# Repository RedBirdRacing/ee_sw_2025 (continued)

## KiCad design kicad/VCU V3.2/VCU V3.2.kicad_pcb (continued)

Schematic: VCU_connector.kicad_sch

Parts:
J1, J2: HD241_24pin

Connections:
+5V: J1.19, J2.3, J2.4; also elsewhere on the board
+12V: J1.1, J1.2, J1.9, J1.10, J1.17, J1.18; also elsewhere on the board
APPS_3VGND: J2.18; also elsewhere on the board
APPS_3VIN: J2.2; also elsewhere on the board
APPS_3VOUT: J2.10; also elsewhere on the board
APPS_5VGND: J2.17; also elsewhere on the board
APPS_5VIN: J2.1; also elsewhere on the board
APPS_5VOUT: J2.9; also elsewhere on the board
BRAKE_AIN: J2.11; also elsewhere on the board
CAN1+: J2.6; also elsewhere on the board
CAN1-: J2.5; also elsewhere on the board
CAN2+: J2.8, J2.16; also elsewhere on the board
CAN2-: J2.7, J2.15; also elsewhere on the board
CAN3+: J2.14; also elsewhere on the board
CAN3-: J2.13; also elsewhere on the board
CURRENT_AIN: J2.12; also elsewhere on the board
DIN_1: J2.21; also elsewhere on the board
DIN_2: J2.22; also elsewhere on the board
DIN_3: J2.23; also elsewhere on the board
GND: J1.7, J1.8, J1.15, J1.16, J1.23, J1.24, J2.19, J2.20; also elsewhere on the board
IGN_12V: J2.24; also elsewhere on the board
PDU_1: J1.3, J1.11; also elsewhere on the board
PDU_2: J1.4, J1.12; also elsewhere on the board
PDU_3: J1.5, J1.13; also elsewhere on the board
PDU_4: J1.6, J1.14; also elsewhere on the board
PDU_5: J1.20; also elsewhere on the board
PDU_6: J1.21; also elsewhere on the board
PDU_7: J1.22; also elsewhere on the board

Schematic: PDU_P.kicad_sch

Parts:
D2: LED; LED_0805_2012Metric_Pad1.45x1.40mm_HandSolder
Q1: MMBT3904; SOT-23
Q2: BSC030P03NS3; Infineon_PG-TDSON-8_6.15x5.15mm
R5, R6, R7: 1k; R_0805_2012Metric_Pad1.20x1.40mm_HandSolder_L
R8: 100k; R_0805_2012Metric_Pad1.20x1.40mm_HandSolder_L

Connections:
+12V: D2.2 (A), Q2.1 (S), Q2.2 (S), Q2.3 (S), R7.1; also elsewhere on the board
/PDU_P4_1/PDU_1/MOS_GATE: Q1.3 (C), Q2.4 (G), R6.2, R7.2, R8.1
/PDU_P4_1/PDU_1/SIGNAL: R5.1; also elsewhere on the board
GND: Q1.2 (E), R8.2; also elsewhere on the board
unnamed: D2.1 (K), R6.1
unnamed: Q1.1 (B), R5.2
PDU_1: Q2.5 (D), Q2.6 (D), Q2.7 (D), Q2.8 (D); also elsewhere on the board

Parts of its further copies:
D3, D4, D5: LED; LED_0805_2012Metric_Pad1.45x1.40mm_HandSolder
Q3, Q5, Q7: MMBT3904; SOT-23
Q4, Q6, Q8: BSC030P03NS3; Infineon_PG-TDSON-8_6.15x5.15mm
R9, R10, R11, R13, R14, R15, R17, R18, R19: 1k; R_0805_2012Metric_Pad1.20x1.40mm_HandSolder_L
R12, R16, R20: 100k; R_0805_2012Metric_Pad1.20x1.40mm_HandSolder_L

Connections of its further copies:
+12V: D3.2 (A), D4.2 (A), D5.2 (A), Q4.1 (S), Q4.2 (S), Q4.3 (S), Q6.1 (S), Q6.2 (S), Q6.3 (S), Q8.1 (S), Q8.2 (S), Q8.3 (S), R11.1, R15.1, R19.1; also elsewhere on the board
/PDU_P4_1/PDU_2/MOS_GATE: Q3.3 (C), Q4.4 (G), R10.2, R11.2, R12.1
/PDU_P4_1/PDU_2/SIGNAL: R9.1; also elsewhere on the board
/PDU_P4_1/PDU_3/MOS_GATE: Q5.3 (C), Q6.4 (G), R14.2, R15.2, R16.1
/PDU_P4_1/PDU_3/SIGNAL: R13.1; also elsewhere on the board
/PDU_P4_1/PDU_4/MOS_GATE: Q7.3 (C), Q8.4 (G), R18.2, R19.2, R20.1
/PDU_P4_1/PDU_4/SIGNAL: R17.1; also elsewhere on the board
GND: Q3.2 (E), Q5.2 (E), Q7.2 (E), R12.2, R16.2, R20.2; also elsewhere on the board
unnamed: D3.1 (K), R10.1
unnamed: D4.1 (K), R14.1
unnamed: D5.1 (K), R18.1
unnamed: Q3.1 (B), R9.2
unnamed: Q5.1 (B), R13.2
unnamed: Q7.1 (B), R17.2
PDU_2: Q4.5 (D); also elsewhere on the board
PDU_3: Q6.5 (D); also elsewhere on the board
PDU_4: Q8.5 (D); also elsewhere on the board

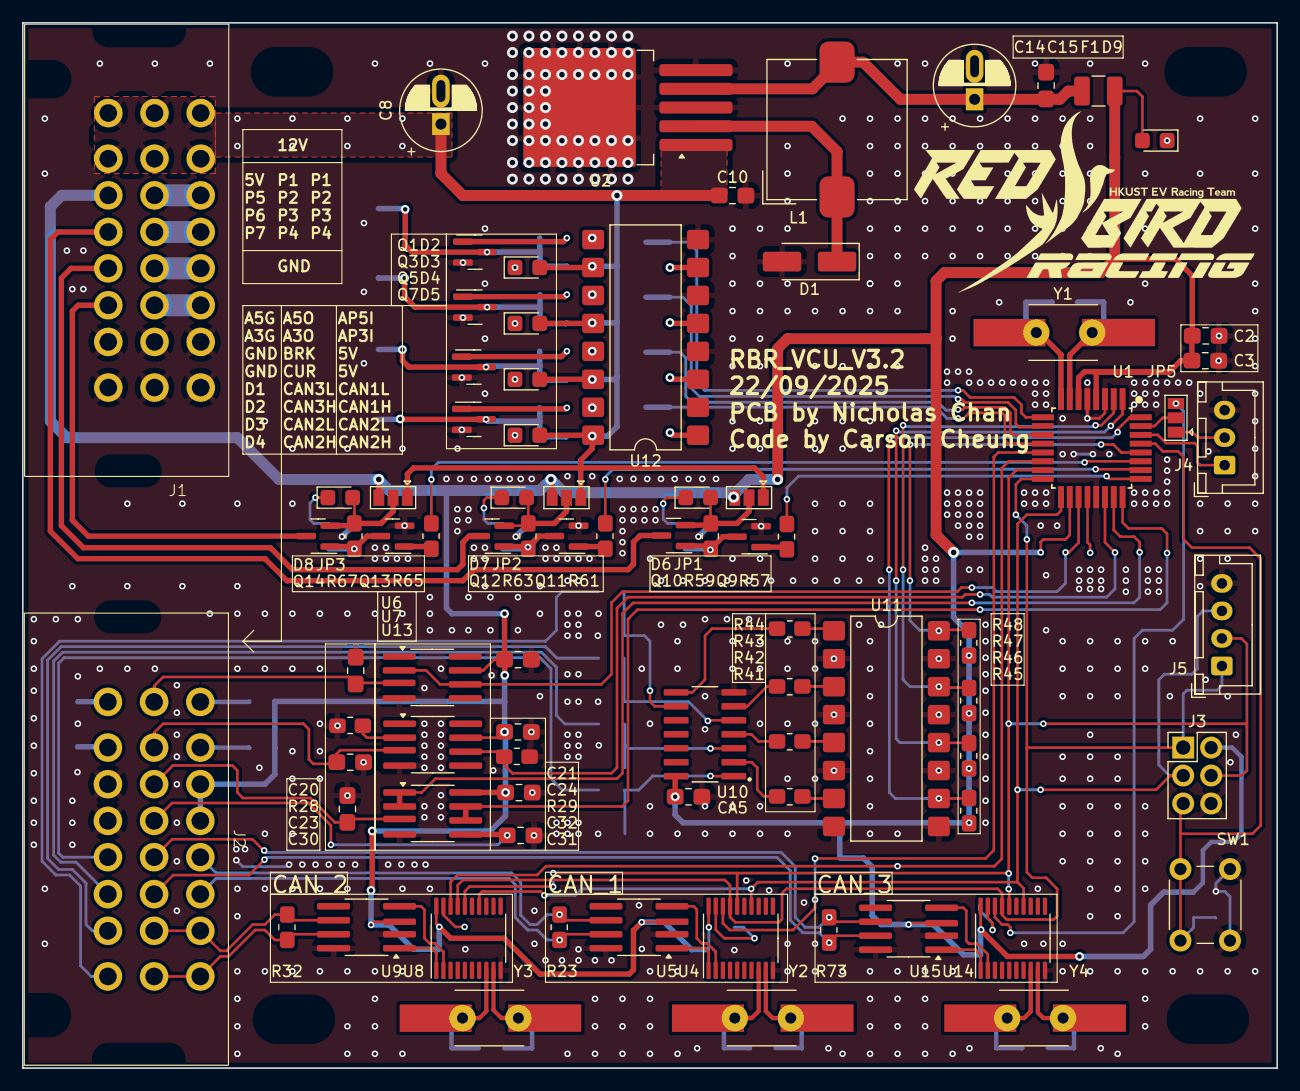
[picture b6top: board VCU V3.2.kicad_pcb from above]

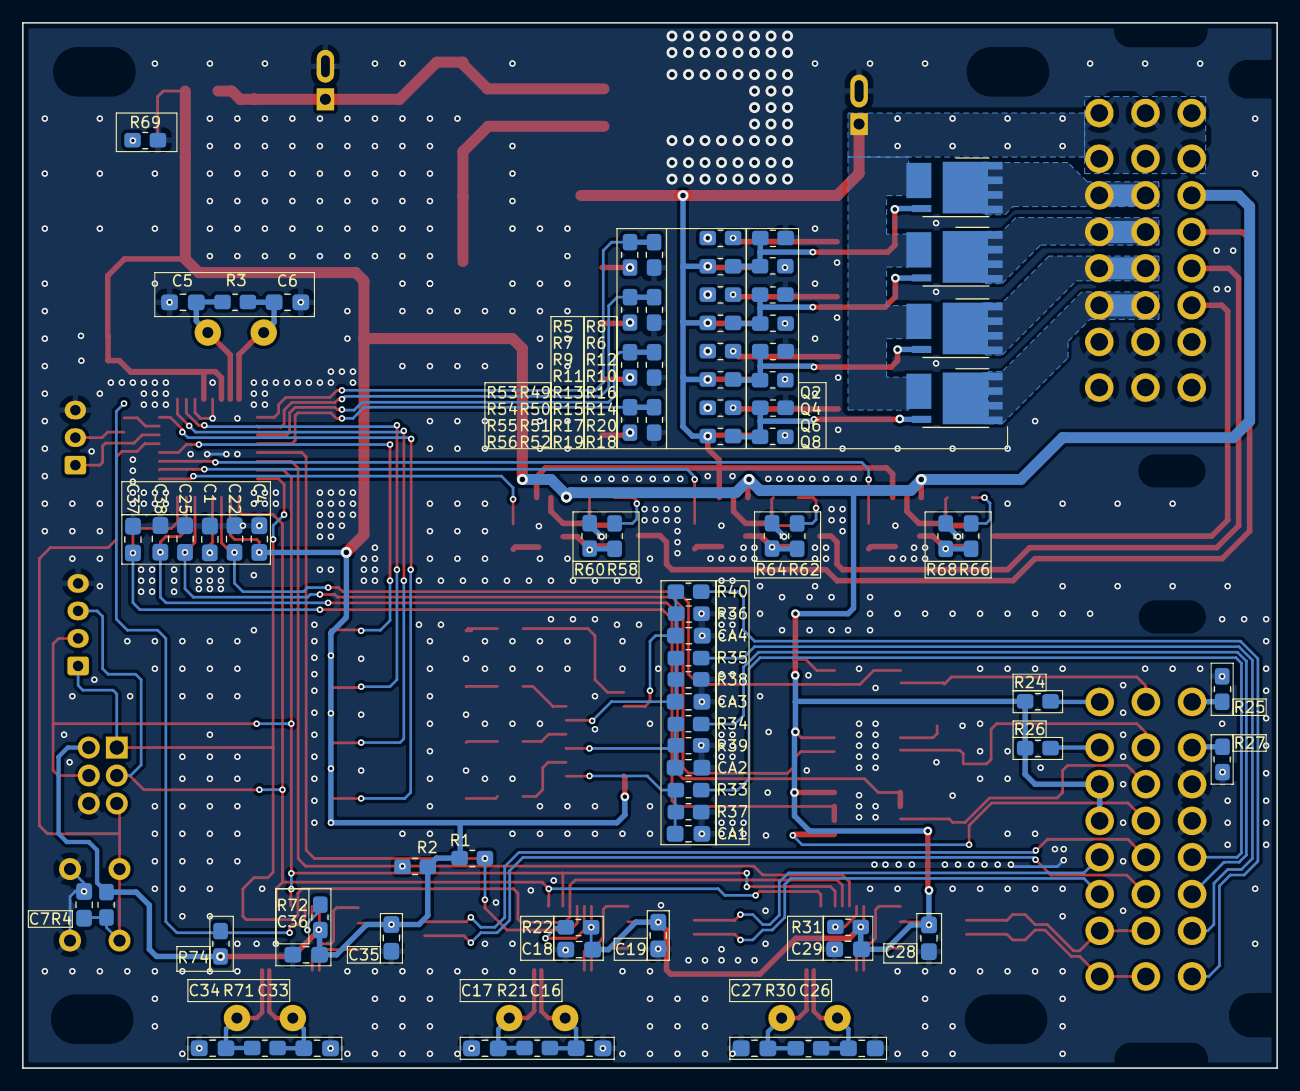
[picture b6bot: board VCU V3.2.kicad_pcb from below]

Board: 2 copper layers, 114.0 x 95.0 mm, 169 parts (83 on the bottom side), 119 nets.

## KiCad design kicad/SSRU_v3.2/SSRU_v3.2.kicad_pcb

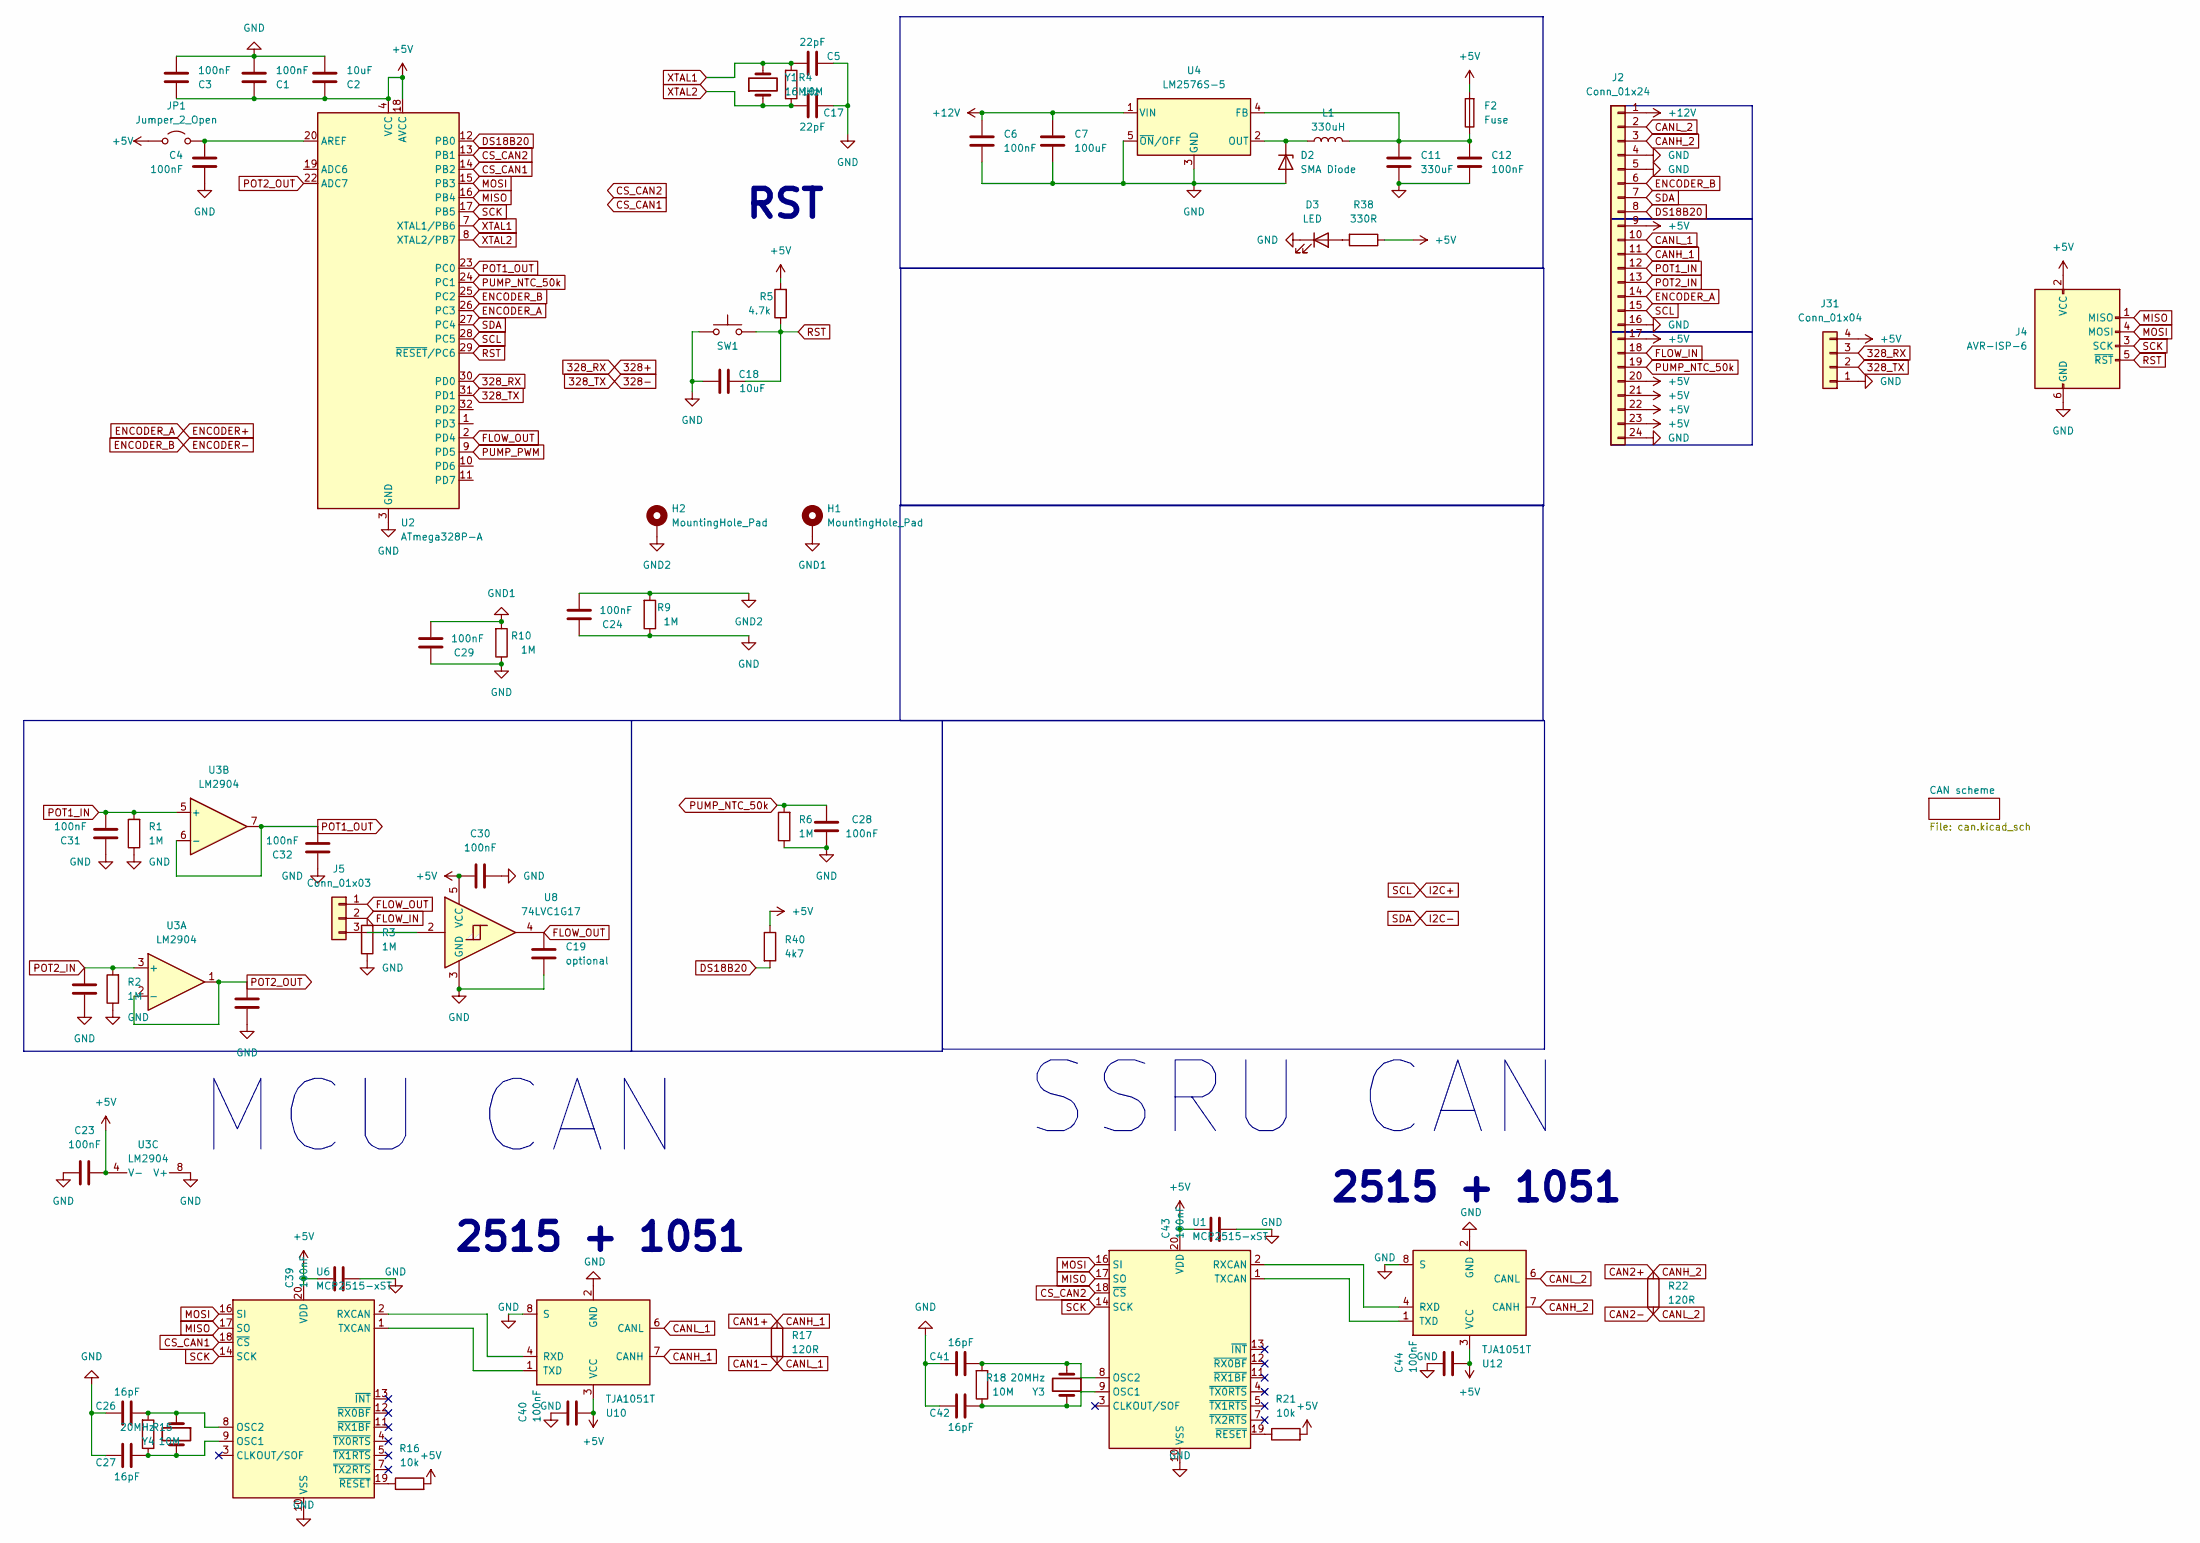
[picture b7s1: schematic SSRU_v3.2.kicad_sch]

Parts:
C1, C3, C4, C6, C12, C23, C24, C28, C29, C30, C31, C32, C36, C37, C39, C40, C43, C44: 100nF; C_0805_2012Metric_Pad1.18x1.45mm_HandSolder_L
C2, C18: 10uF; C_0805_2012Metric_Pad1.18x1.45mm_HandSolder_L
C5, C17: 22pF; C_0805_2012Metric_Pad1.18x1.45mm_HandSolder_L
C7: 100uF; CP_Radial_D6.3mm_P2.50mm_handsolder
C11: 330uF; CP_Radial_D6.3mm_P2.50mm_handsolder
C19: optional; C_0805_2012Metric_Pad1.18x1.45mm_HandSolder_L
C26, C27, C41, C42: 16pF; C_0805_2012Metric_Pad1.18x1.45mm_HandSolder_L
D2: SMA Diode; D_SMA_Handsoldering
D3: LED; LED_0805_2012Metric_Pad1.45x1.40mm_HandSolder
F2: Fuse; Fuse_1210_3225Metric_Pad1.42x2.65mm_HandSolder
H1, H2: MountingHole_Pad; MountingHole_3.2mm_M3_ISO14580_Pad
J2: Conn_01x24; HD241_24pin
J4: AVR-ISP-6; PinHeader_2x03_P2.54mm_Vertical
J5: Conn_01x03; SolderJumper-3_P1.3mm_Open_Pad1.0x1.5mm
J31: Conn_01x04; JST_XH_B4B-XH-A_1x04_P2.50mm_Vertical
JP1: Jumper_2_Open; SolderJumper-2_P1.3mm_Open_Pad1.0x1.5mm
L1: 330uH; L_10.4x10.4_H4.8
R1, R2, R3, R6, R9, R10: 1M; R_0805_2012Metric_Pad1.20x1.40mm_HandSolder_L
R4, R15, R18: 10M; R_0805_2012Metric_Pad1.20x1.40mm_HandSolder_L
R5: 4.7k; R_0805_2012Metric_Pad1.20x1.40mm_HandSolder_L
R16, R21: 10k; R_0805_2012Metric_Pad1.20x1.40mm_HandSolder_L
R17, R22: 120R; R_0805_2012Metric_Pad1.20x1.40mm_HandSolder_L
R38: 330R; R_0805_2012Metric_Pad1.20x1.40mm_HandSolder_L
R40: 4k7; R_0805_2012Metric_Pad1.20x1.40mm_HandSolder_L
SW1: SW_Push; SW_PUSH_6mm_H5mm
U1, U6: MCP2515-xST; TSSOP-20_4.4x6.5mm_P0.65mm
U2: ATmega328P-A; TQFP-32_7x7mm_P0.8mm_L
U3: LM2904; SOIC-8_3.9x4.9mm_P1.27mm_RMC_Handsolder
U4: LM2576S-5; TO-263-5_TabPin3_Handsolder
U8: 74LVC1G17; SOT-23-5_HandSoldering_Extended_RMC
U10, U12: TJA1051T; SOIC-8_3.9x4.9mm_P1.27mm_RMC_Handsolder
Y1: 16MHz; Crystal_HC49-U_Vertical_W_SMD
Y3, Y4: 20MHz; Crystal_HC49-U_Vertical_W_SMD

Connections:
328+: J31.3, U2.30 (PD0)
328-: J31.2, U2.31 (PD1)
+5V: C1.2, C2.2, C3.2, C23.2, C30.2, C39.2, C40.1, C43.2, C44.1, F2.2, J2.9, J2.17, J2.20, J2.21, J2.22, J2.23, J4.2 (VCC), J31.4, JP1.1 (A), R5.2, R16.2, R21.2, R38.1, R40.1, U1.20 (VDD), U2.4 (VCC), U2.6 (VCC), U2.18 (AVCC), U3.4 (V-), U6.20 (VDD), U8.5 (VCC), U10.3 (VCC), U12.3 (VCC)
+12V: C6.2, C7.1, J2.1, U4.1 (VIN)
CAN1+: J2.11, R17.2, U10.7 (CANH)
CAN1-: J2.10, R17.1, U10.6 (CANL)
CAN2+: J2.3, R22.2, U12.7 (CANH)
CAN2-: J2.2, R22.1, U12.6 (CANL)
CS_CAN1: U2.14 (PB2), U6.18 (~CS)
CS_CAN2: U1.18 (~CS), U2.13 (PB1)
DS18B20: J2.8, R40.2, U2.12 (PB0)
ENCODER+: J2.14, U2.26 (PC3)
ENCODER-: J2.6, U2.25 (PC2)
FLOW_IN: J2.18, J5.2, R3.2
FLOW_OUT: C19.2, J5.1, U2.2 (PD4), U8.4
GND: C1.1, C2.1, C3.1, C4.1, C5.1, C6.1, C7.2, C11.2, C12.1, C17.1, C18.1, C19.1, C23.1, C24.1, C26.1, C27.1, C28.2, C29.1, C30.1, C31.1, C32.1, C36.1, C37.1, C39.1, C40.2, C41.1, C42.1, C43.1, C44.2, D2.2 (A), D3.1 (K), J2.4, J2.5, J2.16, J2.24, J4.6 (GND), J31.1, R1.1, R2.1, R3.1, R6.1, R9.1, R10.1, SW1.1, U1.10 (VSS), U2.3 (GND), U2.5 (GND), U2.21 (GND), U3.8 (V+), U4.3 (GND), U4.5 (~ON/OFF), U6.10 (VSS), U8.3 (GND), U10.2 (GND), U10.8 (S), U12.2 (GND), U12.8 (S)
GND1: C29.2, H1.1, R10.2
GND2: C24.2, H2.1, R9.2
I2C+: J2.15, U2.28 (PC5)
I2C-: J2.7, U2.27 (PC4)
MISO: J4.1 (MISO), U1.17 (SO), U2.16 (PB4), U6.17 (SO)
MOSI: J4.4 (MOSI), U1.16 (SI), U2.15 (PB3), U6.16 (SI)
unnamed: D2.1 (K), L1.1, U4.2 (OUT)
unnamed: D3.2 (A), R38.2
unnamed: J5.3, U8.2
unnamed: C4.2, JP1.2 (B), U2.20 (AREF)
unnamed: C42.2, R18.1, U1.9 (OSC1), Y3.2
unnamed: C41.2, R18.2, U1.8 (OSC2), Y3.1
unnamed: U1.2 (RXCAN), U12.4 (RXD)
unnamed: U1.1 (TXCAN), U12.1 (TXD)
unnamed: R21.1, U1.19 (~RESET)
unnamed: C11.1, C12.2, F2.1, L1.2, U4.4 (FB)
unnamed: C27.2, R15.1, U6.9 (OSC1), Y4.2
unnamed: C26.2, R15.2, U6.8 (OSC2), Y4.1
unnamed: R16.1, U6.19 (~RESET)
unnamed: U6.2 (RXCAN), U10.4 (RXD)
unnamed: U6.1 (TXCAN), U10.1 (TXD)
POT1_IN: C31.2, J2.12, R1.2, U3.5 (+)
POT1_OUT: C32.2, U2.23 (PC0), U3.6 (-), U3.7
POT2_IN: C36.2, J2.13, R2.2, U3.3 (+)
POT2_OUT: C37.2, U2.22 (ADC7), U3.1, U3.2 (-)
PUMP_NTC_50k: C28.1, J2.19, R6.2, U2.24 (PC1)
PUMP_PWM: U2.9 (PD5)
RST: C18.2, J4.5 (~RST), R5.1, SW1.2, U2.29 (~RESET/PC6)
SCK: J4.3 (SCK), U1.14 (SCK), U2.17 (PB5), U6.14 (SCK)
XTAL1: C5.2, R4.2, U2.7 (XTAL1/PB6), Y1.2
XTAL2: C17.2, R4.1, U2.8 (XTAL2/PB7), Y1.1

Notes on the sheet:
MCU CAN
2515 + 1051
RST
SSRU CAN

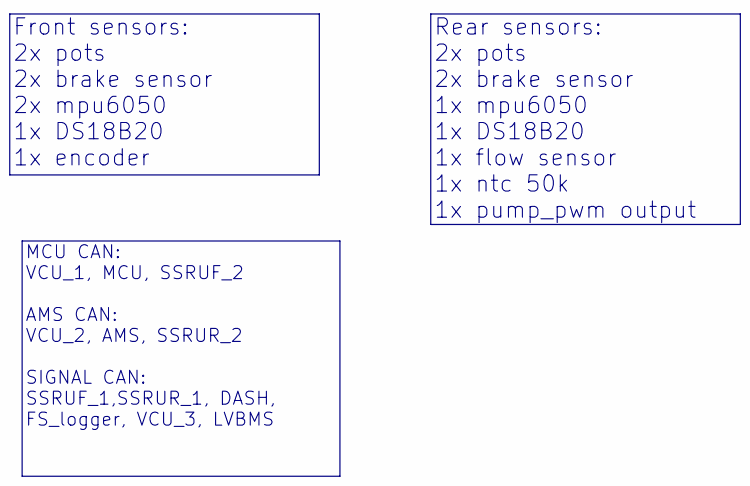
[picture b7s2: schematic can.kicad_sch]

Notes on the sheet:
Front sensors: 2x pots 2x brake sensor 2x mpu6050 1x DS18B20 1x encoder
Rear sensors: 2x pots 2x brake sensor 1x mpu6050 1x DS18B20 1x flow sensor 1x ntc 50k 1x pump_pwm output
MCU CAN: VCU_1, MCU, SSRUF_2 AMS CAN: VCU_2, AMS, SSRUR_2 SIGNAL CAN: SSRUF_1,SSRUR_1, DASH, FS_logger, VCU_3, LVBMS

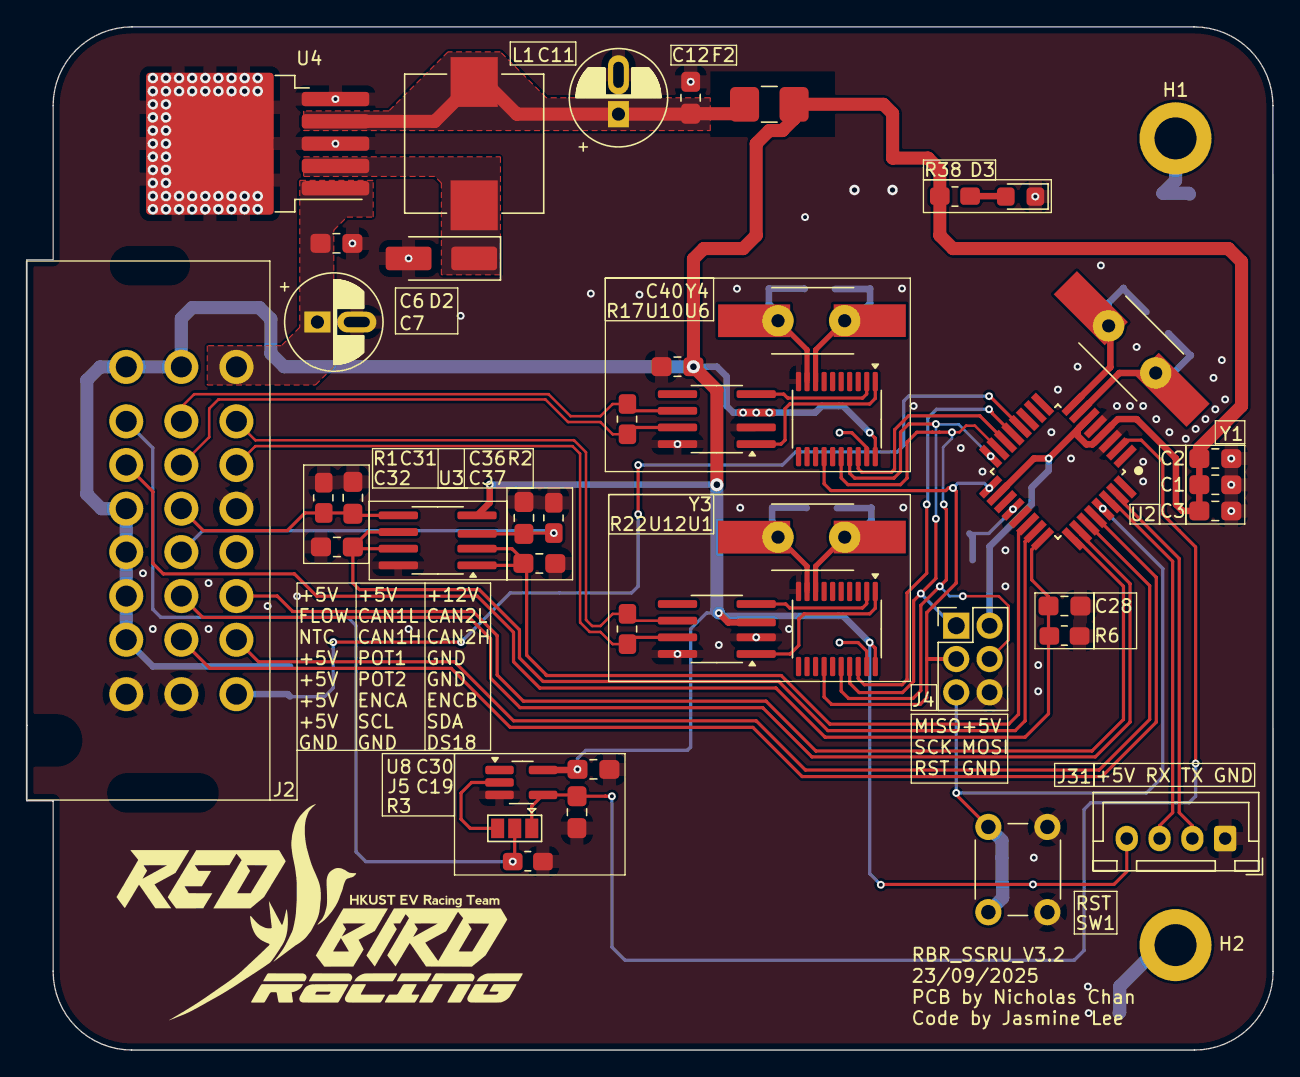
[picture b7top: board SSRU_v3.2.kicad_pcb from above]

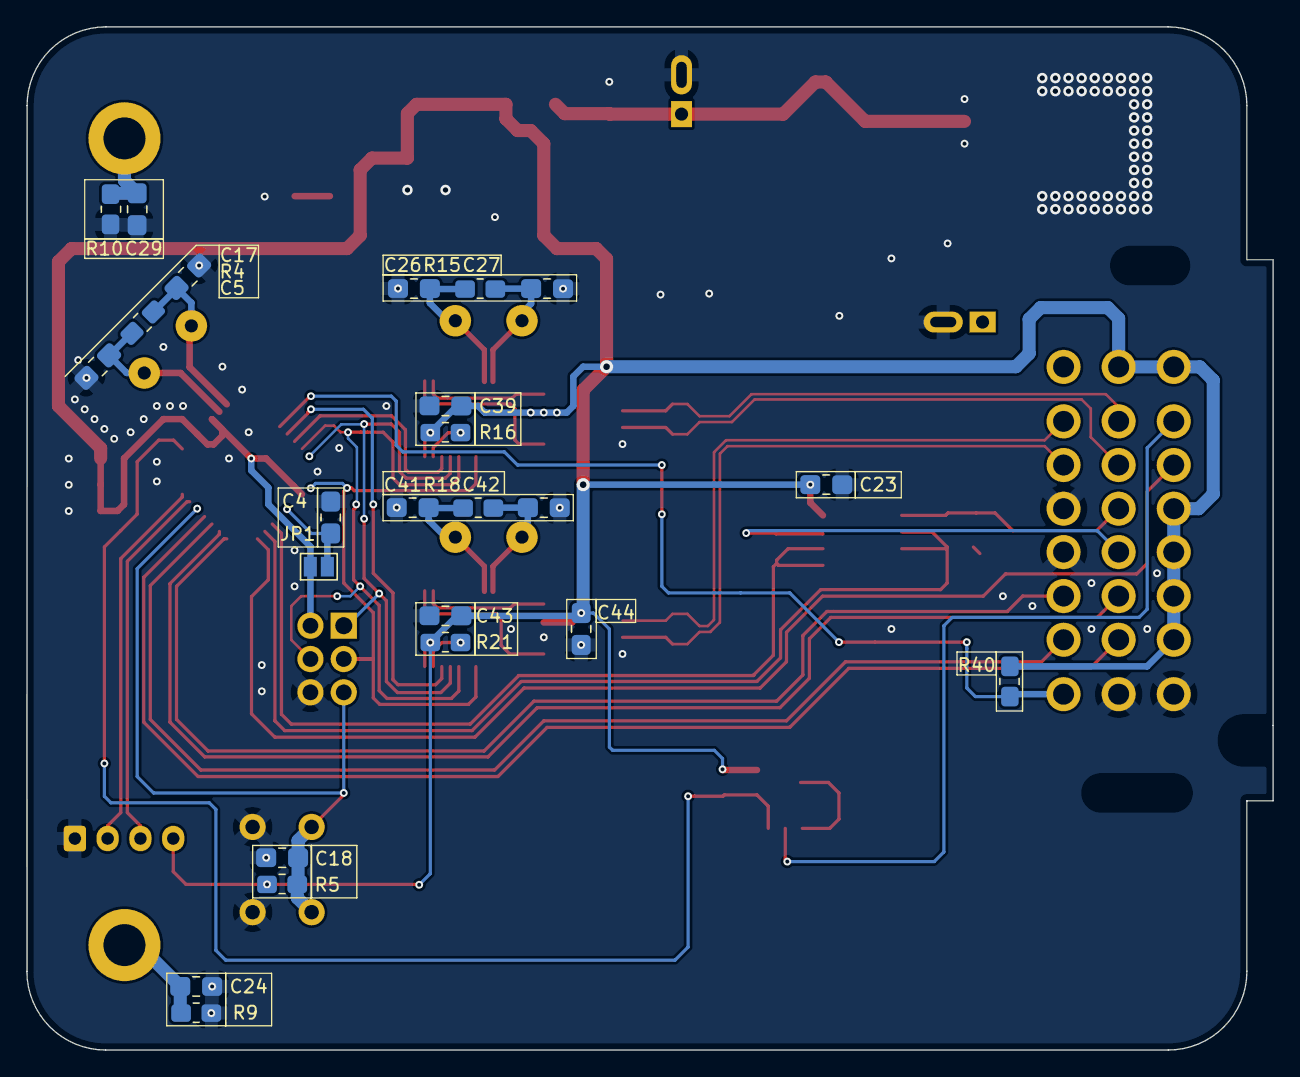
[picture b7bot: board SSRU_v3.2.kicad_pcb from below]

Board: 2 copper layers, 95.0 x 78.0 mm, 68 parts (24 on the bottom side), 46 nets.

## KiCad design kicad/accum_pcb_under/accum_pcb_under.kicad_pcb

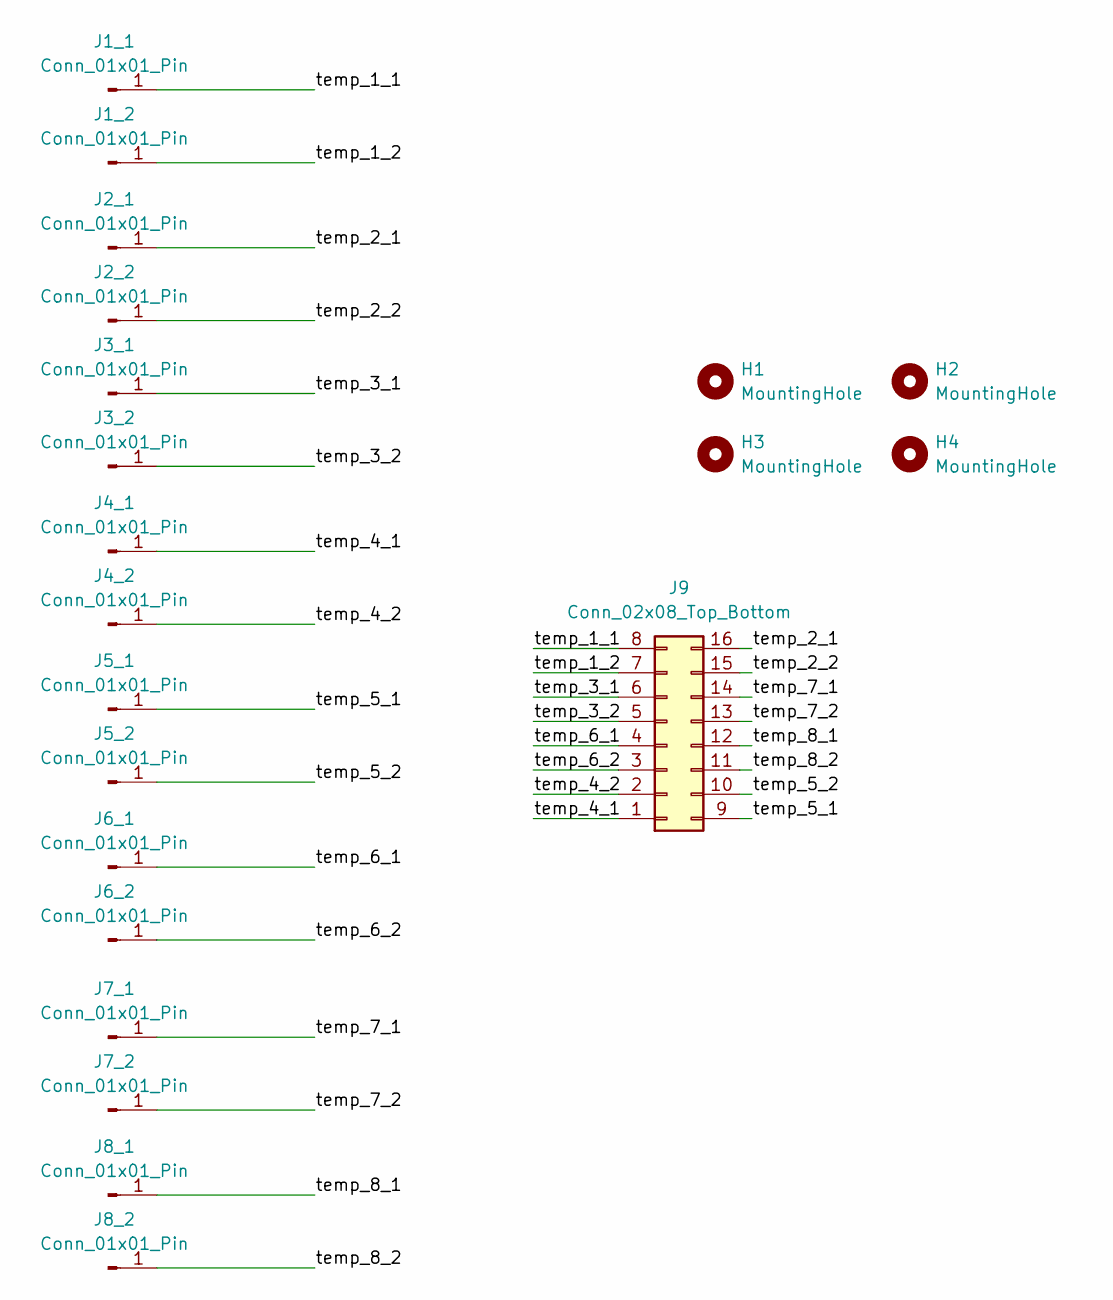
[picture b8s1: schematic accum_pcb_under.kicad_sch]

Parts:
H1, H2, H3, H4: MountingHole; MountingHole_4.3mm_M4
J1_1, J1_2, J2_1, J2_2, J3_1, J3_2, J4_1, J4_2, J5_1, J5_2, J6_1, J6_2, J7_1, J7_2, J8_1, J8_2: Conn_01x01_Pin; PinHeader_1x01_P2.00mm_Vertical
J9: Conn_02x08_Top_Bottom; Molex_Micro-Fit_3.0_43045-1612_2x08_P3.00mm_Vertical

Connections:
/temp_1_1: J1_1.1, J9.8
/temp_1_2: J1_2.1, J9.7
/temp_2_1: J2_1.1, J9.16
/temp_2_2: J2_2.1, J9.15
/temp_3_1: J3_1.1, J9.6
/temp_3_2: J3_2.1, J9.5
/temp_4_1: J4_1.1, J9.1
/temp_4_2: J4_2.1, J9.2
/temp_5_1: J5_1.1, J9.9
/temp_5_2: J5_2.1, J9.10
/temp_6_1: J6_1.1, J9.4
/temp_6_2: J6_2.1, J9.3
/temp_7_1: J7_1.1, J9.14
/temp_7_2: J7_2.1, J9.13
/temp_8_1: J8_1.1, J9.12
/temp_8_2: J8_2.1, J9.11

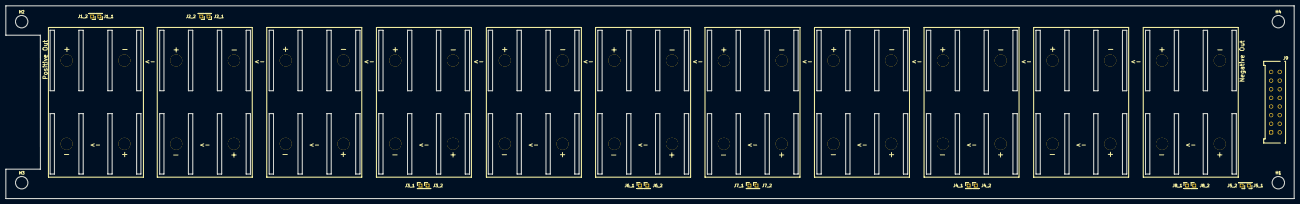
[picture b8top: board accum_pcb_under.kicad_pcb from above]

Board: 4 copper layers, 447.5 x 66.9 mm, 21 parts (0 on the bottom side), 16 nets.

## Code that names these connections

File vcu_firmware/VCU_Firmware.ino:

#include "pinMap.h"
#include <can.h>
// #include <SPI.h>
#include <mcp2515.h>

// uint8_t pin_in[8] = {ADC1, ADC2};
// uint8_t pin_out[8] = {BTN1, BTN2, BTN3, BTN4, LED1, LED2, LED3};

// MCP2515 mcp2515(PB2); // CS pin PC0; PB2 for testing on arduino uno
MCP2515 mcp2515(10);

struct can_frame tx_throttle_msg;
struct can_frame rx_msg;

const float MAX_THROTTLE_IN_VOLT = 4.3;
const float MIN_THROTTLE_IN_VOLT = 0.7;
const float THROTTLE_LOWER_DEADZONE_MAX_IN_VOLT = 0.5;
const float THORTTLE_UPPER_DEADZONE_MIN_IN_VOLT = 4.5;

const int MAX_THROTTLE_OUT_VAL = 32760; // Maximum torque value is 32760 for mcp2515
const int MIN_THROTTLE_OUT_VAL = 300; // Minium torque value tested is 300 (TBC)

uint16_t get_throttle_torque_val()
{
    return MIN_THROTTLE_OUT_VAL;
    float throttle_volt = analogRead(ADC1) / 1024 * 5; // Converts analogRead output to a float between 0V and 5V

    uint16_t ret = 0;

    /*
    Between 0V and THROTTLE_LOWER_DEADZONE_MIN_IN_VOLT: Error for open circuit
    Between THROTTLE_LOWER_DEADZONE_MIN_IN_VOLT and MIN_THROTTLE_IN_VOLT: 0% Torque
    Between MIN_THROTTLE_IN_VOLT and MAX_THROTTLE_IN_VOLT: Linear relationship 
    Between MAX_THROTTLE_IN_VOLT and THORTTLE_UPPER_DEADZONE_MIN_IN_VOLT: 100% Torque
    Between THORTTLE_UPPER_DEADZONE_MIN_IN_VOLT and 5V: Error for short circuit
    */
    if (throttle_volt < THROTTLE_LOWER_DEADZONE_MAX_IN_VOLT)
        ret = 0;
    else if (throttle_volt < MIN_THROTTLE_IN_VOLT) 
        ret = MIN_THROTTLE_OUT_VAL;
    else if (throttle_volt < MAX_THROTTLE_IN_VOLT)
        // Scale up the value for canbus
        ret = (throttle_volt - MIN_THROTTLE_IN_VOLT) / (MAX_THROTTLE_IN_VOLT - MIN_THROTTLE_IN_VOLT) * MAX_THROTTLE_OUT_VAL;
    else if (throttle_volt < THORTTLE_UPPER_DEADZONE_MIN_IN_VOLT)
        ret = MAX_THROTTLE_OUT_VAL;
    else
        ret = 0;

    return ret;
}

uint16_t update_can_tx_throttle_msg()
{
    // Set the can_frame according to the torque map
    uint16_t throttle_torque_val = get_throttle_torque_val();

    // if (throttle_torque_val == 0) // Error in reading torque value
    //   return 1;

    tx_throttle_msg.can_id = 201;
    tx_throttle_msg.can_dlc = 3;
    tx_throttle_msg.data[0] = 0x90; //0x90 for torque, 0x31 for speed
    tx_throttle_msg.data[1] = throttle_torque_val % 0xFF;
    tx_throttle_msg.data[2] = (throttle_torque_val >> 8) & 0xFF;

    return 0;
}

void setup()
{
    // Init pins
    // for (int i = 0; i <  2; i++)
    //     pinMode(pin_in[i], INPUT);
    // for (int i = 0; i < 7; i++)
    //     pinMode(pin_out[i], OUTPUT);

    // Init mcp2515 
    mcp2515.reset();
    mcp2515.setBitrate(CAN_500KBPS, MCP_8MHZ); // 8MHZ for testing on uno
    mcp2515.setNormalMode();
    // while (!Serial);
    //   Serial.begin(9600);
}

void loop()
{
    // Send throttle torque msg if no error
    // if (update_can_tx_throttle_msg() == 0)
        // mcp2515.sendMessage(&tx_throttle_msg);
    tx_throttle_msg.can_id = 201;
    tx_throttle_msg.can_dlc = 3;
    tx_throttle_msg.data[0] = 0x90; //0x90 for torque, 0x31 for speed
    tx_throttle_msg.data[1] = 0x28;
    tx_throttle_msg.data[2] = 0x19;
    mcp2515.sendMessage(&tx_throttle_msg);
    
    // Serial.println("Example: Write to CAN");
    // Serial.println(temp.data[0]);

    delay(100);

    // mcp2515.sendMessage(&tx_throttle_msg);
    // uint32_t lastLEDtick = 0;
    // if (mcp2515.readMessage(&rx_msg) == MCP2515::ERROR_OK)
    // {
    //     // Commented out as currenlty no need to include receive functionality
    //     // if (rx_msg.can_id == 0x522)
    //     //     for (int i = 0; i < 8; i++)
    //     //         digitalWrite(pin_out[i], (rx_msg.data[0] >> i) & 0x01);
    // }
}

// #include "Pedal.h"
// #include "pinMap.h"

// #include <can.h>
// #include <mcp2515.h>

// Pedal throttle(ADC1, ADC2, millis(), 256);

// void setup() {
//   Serial.begin(115200);
// }

// void loop() {
//   throttle.pedalUpdate(millis());
// }
// #include <mcp_canbus.h>
// // #include <mcp2515.h>
// #include <SPI.h>

// // uint8_t pinout[8] = {PA0, PA1, PA3, PA7, PB0, PB1, PB2, PB3};


// #define CAN_500KBPS
// const int SPI_CS_PIN = PB2;
// // MCP_CAN mcp2515(SPI_CS_PIN); 
// MCP2515 mcp2515(SPI_CS_PIN);

// void setup(){
    
// //     // pinMode(PB6, INPUT);

//     // for(int i = 0; i < 8; i++){
//     //     pinMode(pinout[i], OUTPUT);
//     // }

//     mcp2515.reset();
//     mcp2515.setBitrate(CAN_500KBPS, MCP_8MHZ);
//     mcp2515.setBitrate(CAN_500KBPS, MCP_8MHZ);
//     mcp2515.setNormalMode();

//     struct can_frame tx_msg;
//     tx_msg.can_id = 0x520;
//     tx_msg.can_dlc = 3;
//     tx_msg.data[0] = 0x11;
//     tx_msg.data[1] = 0x22;
//     tx_msg.data[2] = 0x33;
//     mcp2515.sendMessage(&tx_msg);

//     struct can_frame rx_msg;

//     uint32_t lastLEDtick = 0;

//     while (1){
        
//         if(mcp2515.readMessage(&rx_msg) == MCP2515::ERROR_OK){
//             if(rx_msg.can_id == 0x522){

//                 // for(int i = 0; i < 8; i++){
//                 //     digitalWrite(pinout[i], (rx_msg.data[0] >> i) & 0x01);
//                 // }

//                 mcp2515.sendMessage(&tx_msg);
//             }
//         }
//     }
// }

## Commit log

2025-01-05 Initial commit
    Added folders
2025-01-06 added files from GEN 5 CAD
2025-01-08 file structure
2025-01-09 TSAL-R v3.0
    Redesigned the TSAL-R, currently v3. with naming RBR-TSAL-R v3.0
2025-01-09 TSAL-G v3.0 New PCB design for TSAL-G, with changes for TLV431 for both TSAL-R and TSAL-G
2025-01-10 LED drive v2.0
    redesigned the mos cus the old one probably doesn't work
2025-01-10 LED_Driver_v3.0
2025-01-11 hole seperation to multiples of 3mm
2025-01-13 Sensor board redesign
2025-01-15 nothing to do
2025-01-22 Incomplete firmware for the VCU
    Some libraries are written for the VCU, including initialization for pedal objects and libraries for simple DSP(incomplete and buggy).
2025-01-23 tsal_r V4
2025-02-06 sensor boardvoltage divider
2025-02-06 vcu new pdf
2025-02-07 Basic throttling
2025-02-08 Throttle deadzone
2025-02-09 indicators
2025-02-10 Renamed stuff for readability
    Added more constants and renamed some for controlling torque curve
    Commented parts of code related to receiving msgs from canbus
2025-02-18 vcu_firmware rename
2025-02-21 added indicators v1.05
2025-02-27 printer frame pcb
2025-02-27 v0 2020
2025-02-27 tool head
2025-02-27 frame pcb gerbers
2025-03-06 Init folder
2025-03-06 Init folder
    The .txt file is just a dummy file for having the folder on git
2025-03-06 added link to can bus library
2025-03-07 Sensor board V10
2025-03-07 Removed unneeded testing code
2025-03-07 Fixed incorrect max throttle bug
2025-03-07 Merged code into phillip's library
    Simplified the main file (vcu_firmware.ino) by moving logic for pedal into pedal.cpp and pedal.h
2025-03-07 Functionality to check for invalid pedal input
    Added functionality to check for invalid pedal values.
    Not yet added response to invalid pedal values.
2025-03-08 Sensor Board V10 schematics
2025-03-09 Sensor Board V10.0 done
2025-03-11 file structure of vcu firmware
2025-03-19 vcu v2
2025-03-20 sensor board v10 gerbers
2025-03-27 precharge relay
2025-03-27 created TSAL_GR_v1
2025-04-11 Reverse direction, start procedure
2025-04-12 initial commit for Torque Vectoring / Teensy Control
2025-04-13 Incremental Control
    Tried to implement incremental control
    Torque reduction is applying every cycle instead of a set value
    Needs revision on logic, probably broken, asked GPT to redo some bits because brain melted and don't want to rewrite some parts to deal with the change to an incremental framework
2025-04-14 Updated pinmap for custom VCU pcb
2025-04-19 19/4 stuff
    Changed from queue to cyclic buffer @Planeson
    Changed from size 128 FIR filter to size 16 Average filter
    Fixed some potential bugs related to uint16_t and int16_t @Planeson
    Fixed some potential bugs related to millis unsigned long @LkNETWORK @Planeson
    Fixed some bugs with float and int
    Reworked the definitions of deadzones in throttle pedal inputs
2025-04-19 Spelling update
2025-04-19 Debug flag update
2025-04-20 Debug functionality
    Added Debug functionality as suggested by @Planeson
    Grouped the debug functions into debug.h for easy access and update
2025-04-20 Spelling :)
2025-04-20 Revert "Debug flag update"
    This reverts commit d20278f4eccd77d0a258ee612af62fe48eed303f.
2025-04-20 Reapply "Debug flag update"
    This reverts commit 15267ddcd7f54db084547141bf70e2540685d89c.
2025-04-20 Revert "Spelling update"
    This reverts commit 4952e99dc5512a663fdda55218ca17b1f4e1ac84.
2025-04-20 More debug update
2025-04-21 Removed torque vectoring and vcu folder
    Removing these folders as we have separate repos for it
2025-04-23 Sensor Board V9
2025-05-07 charging schematics
2025-05-22 ssruv3
2025-06-01 vcu v3
2025-06-04 BDU_LVS done
2025-06-04 BDU_TS
2025-06-05 cccv charger using lt3741 first commit
2025-06-05 removed old SSRU items
2025-06-05 bdu_ts update
2025-06-05 Nicohlas sanity gone
2025-06-06 BDU_TS and LVS v1 done
2025-06-07 SSRU v3 new scheme
2025-06-07 BDU_LVS changes
    Added connector for TSAL-G of contactor Aux
2025-06-08 BDU _TS
    resistor changed from board to external resistor
2025-06-10 BDU _TS gerbers
2025-06-10 updated VCU V2
2025-06-12 idk how to use github
2025-06-13 Redraw PCB
2025-06-13 changed some silkscreen
2025-06-13 gerbes
    DSCHG_TSMP gerbers
2025-06-15 ssru v3
    current to voltage lm324 supply to 5v. icsp header mosi miso fixed
2025-06-23 SSRU new layout
2025-06-27 SSRU new scheme
2025-06-27 added SSRU_v3 zip
2025-06-27 Changed ssru schematics and pdf
    added CH340, Encoder and re assigned ADC.
2025-06-27 SSRU
2025-06-30 created TS schematics
2025-06-30 change connectors, footprints and new layout
2025-07-04 charging circuit
2025-07-05 bunch of schemes
2025-07-05 current to voltage
2025-07-07 SSRU V3
2025-07-08 MCU_scheme
2025-07-10 tsal v4.0.2
2025-07-10 changed tsal_g traces
2025-07-10 updated tsal
2025-07-10 updated layout of tsal, need final touhces
2025-07-10 plausibility check inverted pinout and ERC debug
2025-07-10 Delete kicad/tsal_g_v4.zip/RedBirdRacing ee_sw_2025 main kicad-tsal_g_v4 directory
    minor change
2025-07-10 Plausibility check and ERC debug
    -inverted plausibility check pin out
    -arrange silkscreen reference
    -debug ERC
2025-07-11 TSAL_G final touches
2025-07-13 created SSRU ibom
2025-07-13 Create AccumPCBs
    2 PCBs for the accumulator
2025-07-13 Create Accum_CPBs
2025-07-13 Create AccumPCBs
2025-07-13 AccumPCB_up
2025-07-13 AccumPCB_under
2025-07-16 new schematics
2025-07-21 ts SCHEME AND SSRU
2025-07-21 ssru3.1 pcb edgec ut
2025-07-22 SSRU v3.1 updates
2025-07-23 Updated plausibility latch logic
    need review
2025-07-23 updated plausibility check latch and debugged ts
    inverted tlv431 pad
    connected hv gnd
    removed power cycle reset latch
    add plausibility check latch
    need review
2025-07-23 Debugged tsal r
    inverted tlv431 pad
    connected hv- gnd
2025-07-23 changes in tsal_g
    silkscreen, traces
2025-07-23 tsalR
2025-07-24 updated cd4001
2025-07-25 ssruv3.1
2025-07-25 gerbers
2025-07-30 TS scheme update
2025-08-06 Update PCB layout and backup files
    Removed old backup ZIPs and added new ones for SSRU_v3.1. Adjusted component placements and routing in SSRU_v3.1.kicad_pcb, including changes to footprints, coordinates, and net segments for improved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
2025-08-07 sorry I loved you
2025-08-08 TS schematics
2025-08-12 ssru v3.1
2025-08-12 VCU V3.1 preview (further change needed)
    vcu v3.1
    MCP2515 TSSOP20 package
    ADC input opamp
    AREF to gnd
    CAN isolation
    ch340n&usb c 2.0 UART
2025-08-13 VCU v3.1 changes
2025-08-13 idk what changes
2025-08-14 VCU V3.1 preview patch v2
    DRC debug
    Change to pmos
    remove usb c and add xh
    remap pinout
    rewiring
2025-08-16 schematics
2025-08-17 charging can
2025-09-08 shutdown circuit
2025-09-13 VCU V3.2
2025-09-15 vcuv3.2 haha where
2025-09-19 Tsal g v4.2 review needed
2025-09-19 REMOVED not needed stuffs and added new accum pcb
2025-09-19 AHHHHH vcu v3.2
2025-09-19 ssru v3.2
2025-09-19 haha VCU V3.2 AND NEW SCHEMATICS HAHAHA
2025-09-21 VCU V3.2 FINISH LAYOUT
2025-09-21 VCU V3.2 DONE HAHA
    Do you remember? the 21st night of September.
2025-09-22 VCUV3.2
2025-09-22 stuffs
2025-09-22 Done SSRUV3.2 VCU V3.2
2025-09-25 added IMD & TSMS latch logic
2025-09-26 latch ahhhh
2025-09-26 Draw IMD latch
2025-09-27 file strucutre
2025-09-27 IMD latch with small IMD moutning
2025-09-28 imd latch and LED pull high
2025-09-28 did all 3 boards
2025-10-01 328_3ch_can
2025-10-04 Update TS schematics and SDC wiring, add power symbols
    Removed outdated backup files and made significant updates to the TS schematics, including reworking rectangle regions, global labels, and power symbol placements. Added and adjusted +12V and GND sym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
2025-10-05 Update charging circuit and TS schematics connections
    Removed obsolete backup files and updated global labels in TS schematics. Modified the charging circuit schematic to use a 3-pin connector instead of 4-pin, adjusted wire routing, connector placement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
2025-10-06 Update IMD_TSMS latch PCB layout and generate Gerbers
    Updated the IMD_TSMS_latch_logic PCB layout with multiple component position changes, replaced R32 with D1 (diode), and removed R35. Adjusted mounting hole and connector locations, and generated new 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
2025-11-10 update IMD reset
2025-11-10 pcb layout update
2025-11-29 Updated TSAL G V4.2
    this board already got fabbed
    test is needed
2026-01-07 updated IMD and TSMS latch
2026-01-07 minor update on IMD and TSMS latch
2026-01-08 changed to PMOS to drive relay
2026-01-08 added NO NC to avoid confusion
2026-01-08 added mounting hole, v2 tsms imd latch done
2026-01-08 added BSPD
2026-01-09 minor fix
2026-01-10 added silkscreen
2026-01-10 minor update
